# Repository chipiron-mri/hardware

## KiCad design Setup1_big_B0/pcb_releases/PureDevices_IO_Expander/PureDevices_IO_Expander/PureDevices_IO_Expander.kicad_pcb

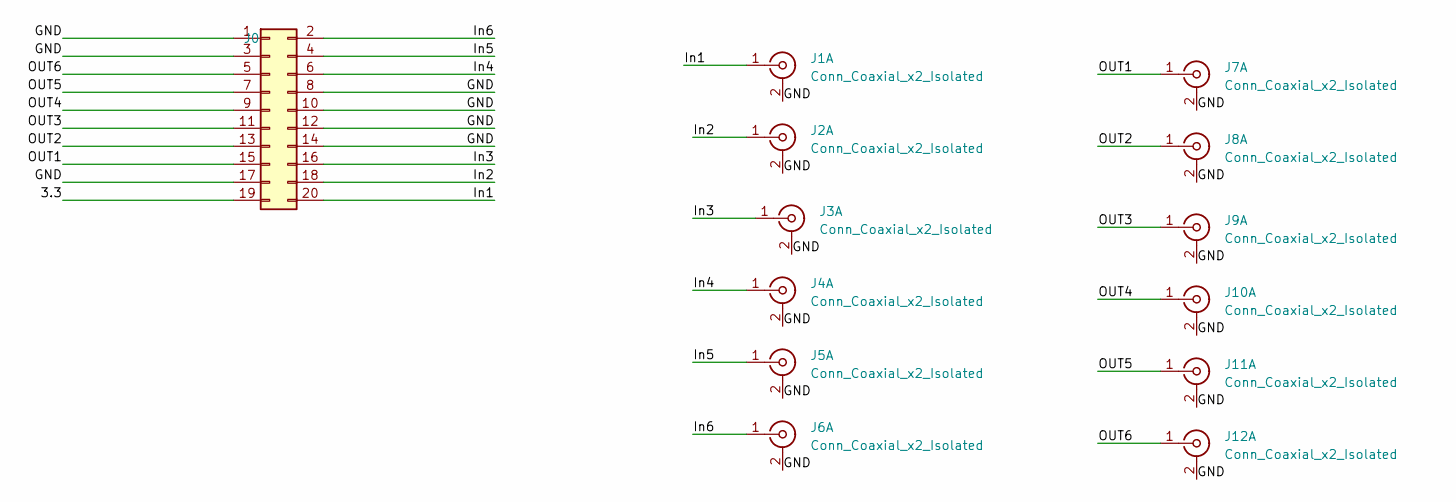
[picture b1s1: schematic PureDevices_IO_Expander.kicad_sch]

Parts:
J0: Conn_02x10_Odd_Even; IDC-Header_2x10_P2.54mm_Vertical
J1, J2, J3, J4, J5, J6, J7, J8, J9, J10, J11, J12: Conn_Coaxial_x2_Isolated; SMB_Jack_Vertical

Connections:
/3.3: J0.19
/GND: J0.1, J0.3, J0.8, J0.10, J0.12, J0.14, J0.17, J1.2 (Ext1), J2.2 (Ext1), J3.2 (Ext1), J4.2 (Ext1), J5.2 (Ext1), J6.2 (Ext1), J7.2 (Ext1), J8.2 (Ext1), J9.2 (Ext1), J10.2 (Ext1), J11.2 (Ext1), J12.2 (Ext1)
/In1: J0.20, J1.1 (In1)
/In2: J0.18, J2.1 (In1)
/In3: J0.16, J3.1 (In1)
/In4: J0.6, J4.1 (In1)
/In5: J0.4, J5.1 (In1)
/In6: J0.2, J6.1 (In1)
/OUT1: J0.15, J7.1 (In1)
/OUT2: J0.13, J8.1 (In1)
/OUT3: J0.11, J9.1 (In1)
/OUT4: J0.9, J10.1 (In1)
/OUT5: J0.7, J11.1 (In1)
/OUT6: J0.5, J12.1 (In1)

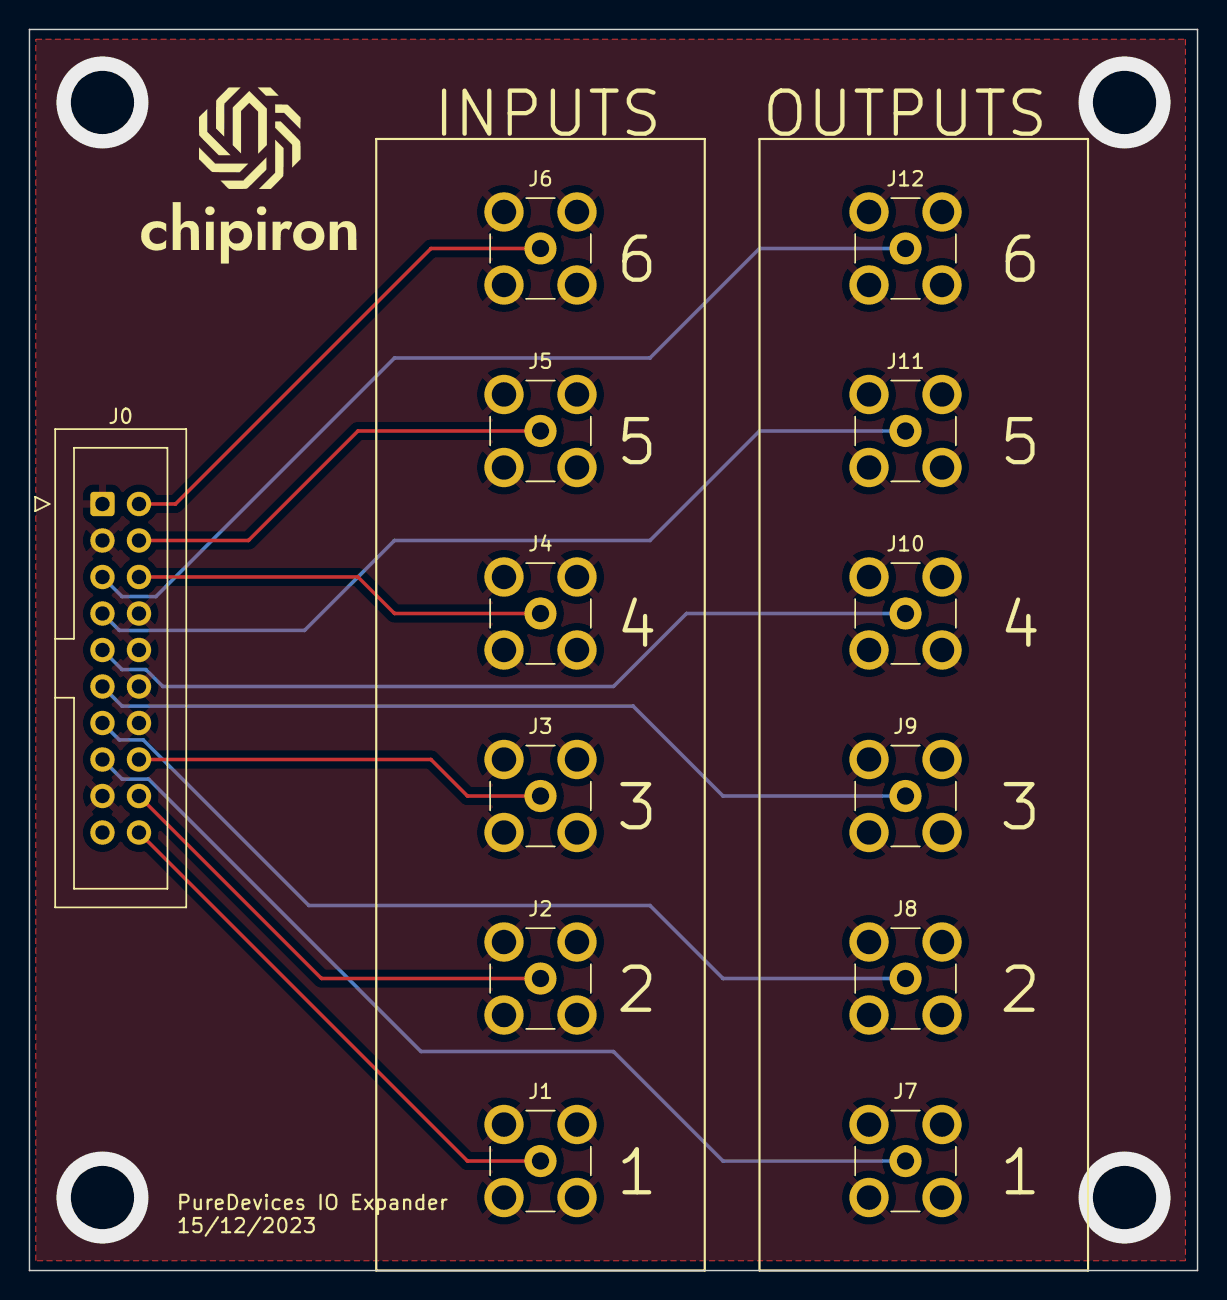
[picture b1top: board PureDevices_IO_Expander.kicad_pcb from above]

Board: 2 copper layers, 81.3 x 86.4 mm, 13 parts (0 on the bottom side), 13 nets.

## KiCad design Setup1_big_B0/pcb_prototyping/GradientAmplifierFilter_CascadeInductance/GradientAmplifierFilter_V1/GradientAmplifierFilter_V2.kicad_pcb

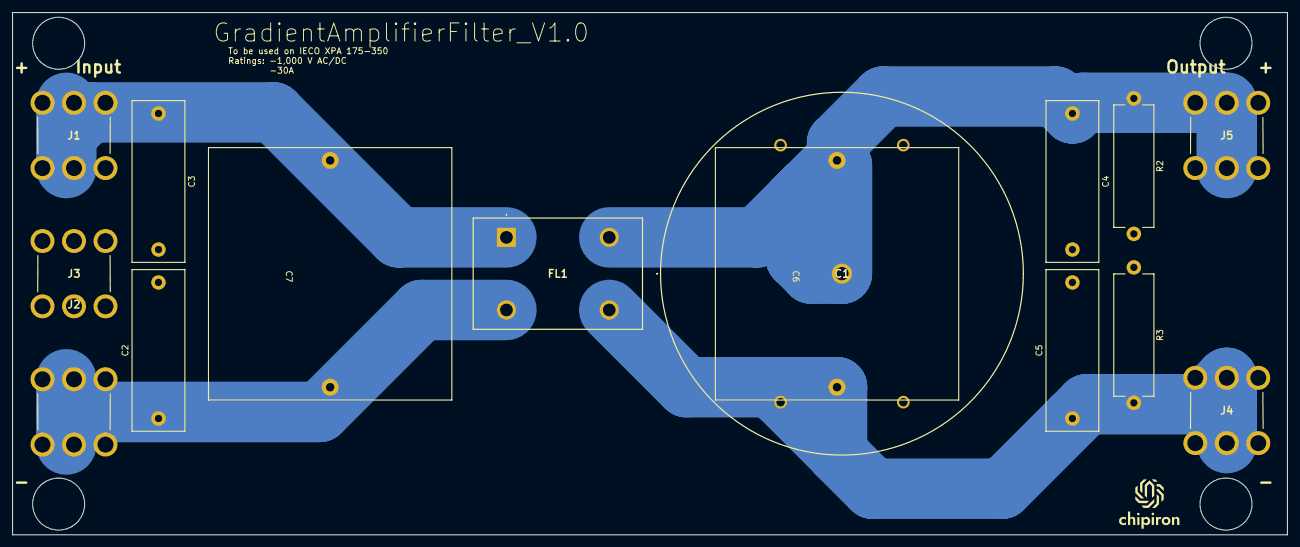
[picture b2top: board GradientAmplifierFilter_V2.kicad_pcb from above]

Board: 4 copper layers, 210.8 x 86.4 mm, 16 parts (0 on the bottom side), 5 nets.

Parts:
   : LOGO
C1: 200uf; B32320I8207K000
C2, C3, C4, C5: 47n; C_Rect_L26.5mm_W8.5mm_P22.50mm_MKS4
C6, C7: 20uf; PHE840ER8100MR08R06L2
FL1: 33uH; SCF19XV3001R9A003JV
J1, J2, J3, J4, J5: 7807
R2, R3: 1Meg; R_Axial_Power_L20.0mm_W6.4mm_P22.40mm

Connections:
Earth: C2.2, C3.2, C4.2, C5.2, J3.1, J3.2, J3.3, J3.4, J3.5, J3.6, R2.2, R3.1
GradientIn+: C3.1, C7.1, FL1.1 (N1_1), J1.1, J1.2, J1.3, J1.4, J1.5, J1.6
GradientIn-: C2.1, C7.2, FL1.2 (N1_2), J2.1, J2.2, J2.3, J2.4, J2.5, J2.6
GradientOut+: C1.1, C4.1, C6.1, FL1.4 (N2_2), J5.1, J5.2, J5.3, J5.4, J5.5, J5.6, R2.1
GradientOut-: C1.2, C1.3, C5.1, C6.2, FL1.3 (N2_1), J4.1, J4.2, J4.3, J4.4, J4.5, J4.6, R3.2

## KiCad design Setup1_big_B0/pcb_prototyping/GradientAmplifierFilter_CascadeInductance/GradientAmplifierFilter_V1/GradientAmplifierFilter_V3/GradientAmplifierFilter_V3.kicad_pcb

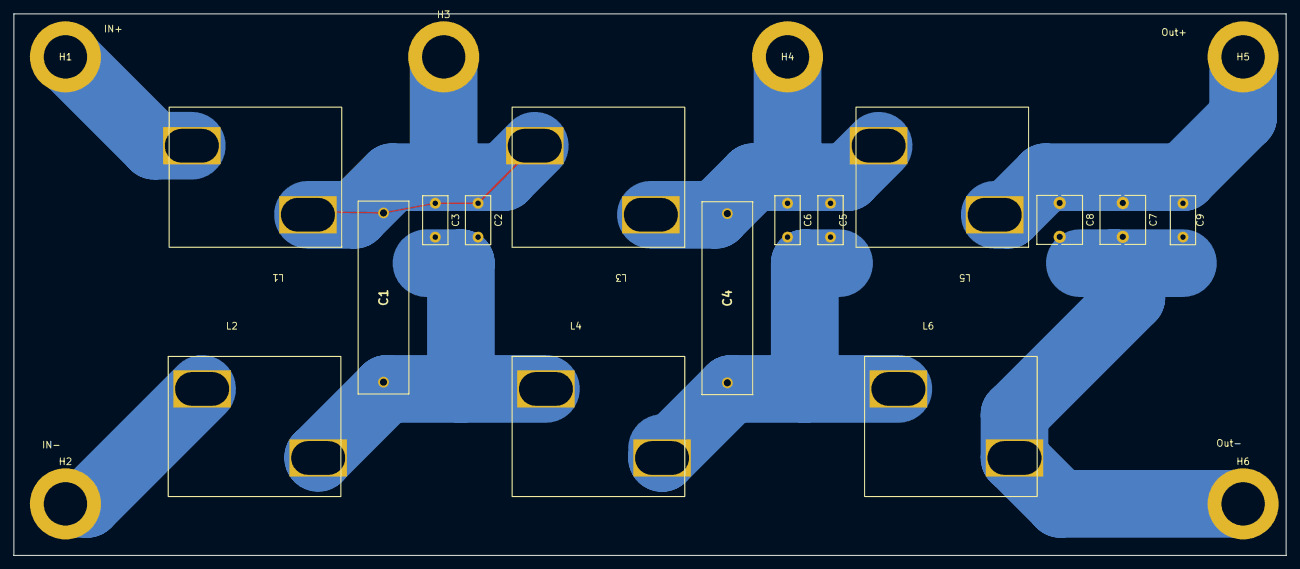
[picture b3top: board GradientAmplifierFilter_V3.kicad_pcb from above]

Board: 2 copper layers, 188.0 x 80.0 mm, 21 parts (0 on the bottom side), 8 nets.

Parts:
C1, C4: C; KTD500B157M99A0B00
C2, C3, C5, C6, C9: CC_Small; C_Rect_L7.0mm_W3.5mm_P5.00mm
C7, C8: C_Small; C_Rect_L7.0mm_W6.5mm_P5.00mm
H1, H2, H3, H4, H5, H6: MountingHole_Pad; MountingHole_6.4mm_M6_ISO7380_Pad
L1, L2, L3, L4, L6: 4.7u; IHDM1008BCEV1R2M3A
L5: 2.2u; IHDM1008BCEV1R2M3A

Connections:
unnamed: C1.1, C2.1, C3.1, H3.1, L1.2, L3.1
unnamed: C1.2, C2.2, C3.2, L2.1, L4.2
unnamed: C4.1, C5.1, C6.1, H4.1, L3.2, L5.1
unnamed: C4.2, C5.2, C6.2, L4.1, L6.2
unnamed: C7.1, C8.1, C9.1, H5.1, L5.2
unnamed: C7.2, C8.2, C9.2, H6.1, L6.1
unnamed: H1.1, L1.1
unnamed: H2.1, L2.2

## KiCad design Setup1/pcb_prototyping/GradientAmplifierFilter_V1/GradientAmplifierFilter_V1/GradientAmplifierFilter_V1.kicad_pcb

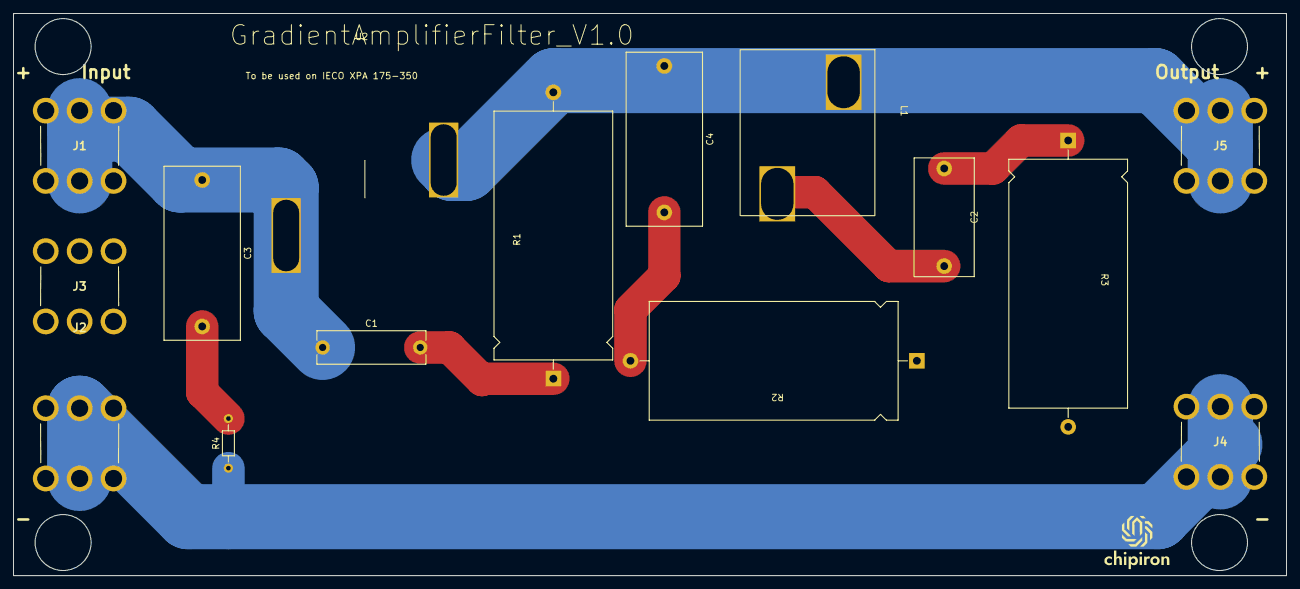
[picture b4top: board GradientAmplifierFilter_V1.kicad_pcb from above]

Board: 4 copper layers, 195.6 x 86.4 mm, 16 parts (0 on the bottom side), 9 nets.

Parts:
   : LOGO
C1: 390p; C_Rect_L16.5mm_W4.9mm_P15.00mm_MKT
C2: 3.9n; C_Rect_L18.0mm_W9.0mm_P15.00mm_FKS3_FKP3
C3, C4: 100n; C_Rect_L26.5mm_W11.5mm_P22.50mm_MKS4
J1, J2, J3, J4, J5: 7807
L1: IHDM1008BCEV100M30; IHDM1008BCEV1R2M3A
R1: 22; Resistor big
R2: 47; Resistor big
R3: 2.2; Resistor big
R4: 200; R_Axial_DIN0204_L3.6mm_D1.6mm_P7.62mm_Horizontal
U2: CPEX3635L-150MC; CPEX3635L

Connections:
Earth: J3.1, J3.2, J3.3, J3.4, J3.5, J3.6, R2.1, R3.2
GradientIn+: C1.1, C3.1, J1.1, J1.2, J1.3, J1.4, J1.5, J1.6, U2.1
GradientIn-: J2.1, J2.2, J2.3, J2.4, J2.5, J2.6, J4.1, J4.2, J4.3, J4.4, J4.5, J4.6, R4.1
GradientOut+: C4.1, J5.1, J5.2, J5.3, J5.4, J5.5, J5.6, L1.2, R1.2, U2.2
unnamed: C1.2, R1.1
unnamed: C2.1, L1.1
unnamed: C2.2, R3.1
unnamed: C3.2, R4.2
unnamed: C4.2, R2.2

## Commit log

2023-11-22 Add first sctruture
2023-11-29 add box to B0 setup and improve setup3
2023-11-30 Finish big coil setup correct box
2023-12-05 cleanning
2023-12-05 Add file settings to B0
2023-12-14 update main folders
2023-12-15 change filename of coil holder
2023-12-18 Commit PureDevices_IO
2024-01-03 Add gradient XY
